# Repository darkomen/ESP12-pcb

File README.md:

# ESP12-pcb
Pcb for use an ESP12-e

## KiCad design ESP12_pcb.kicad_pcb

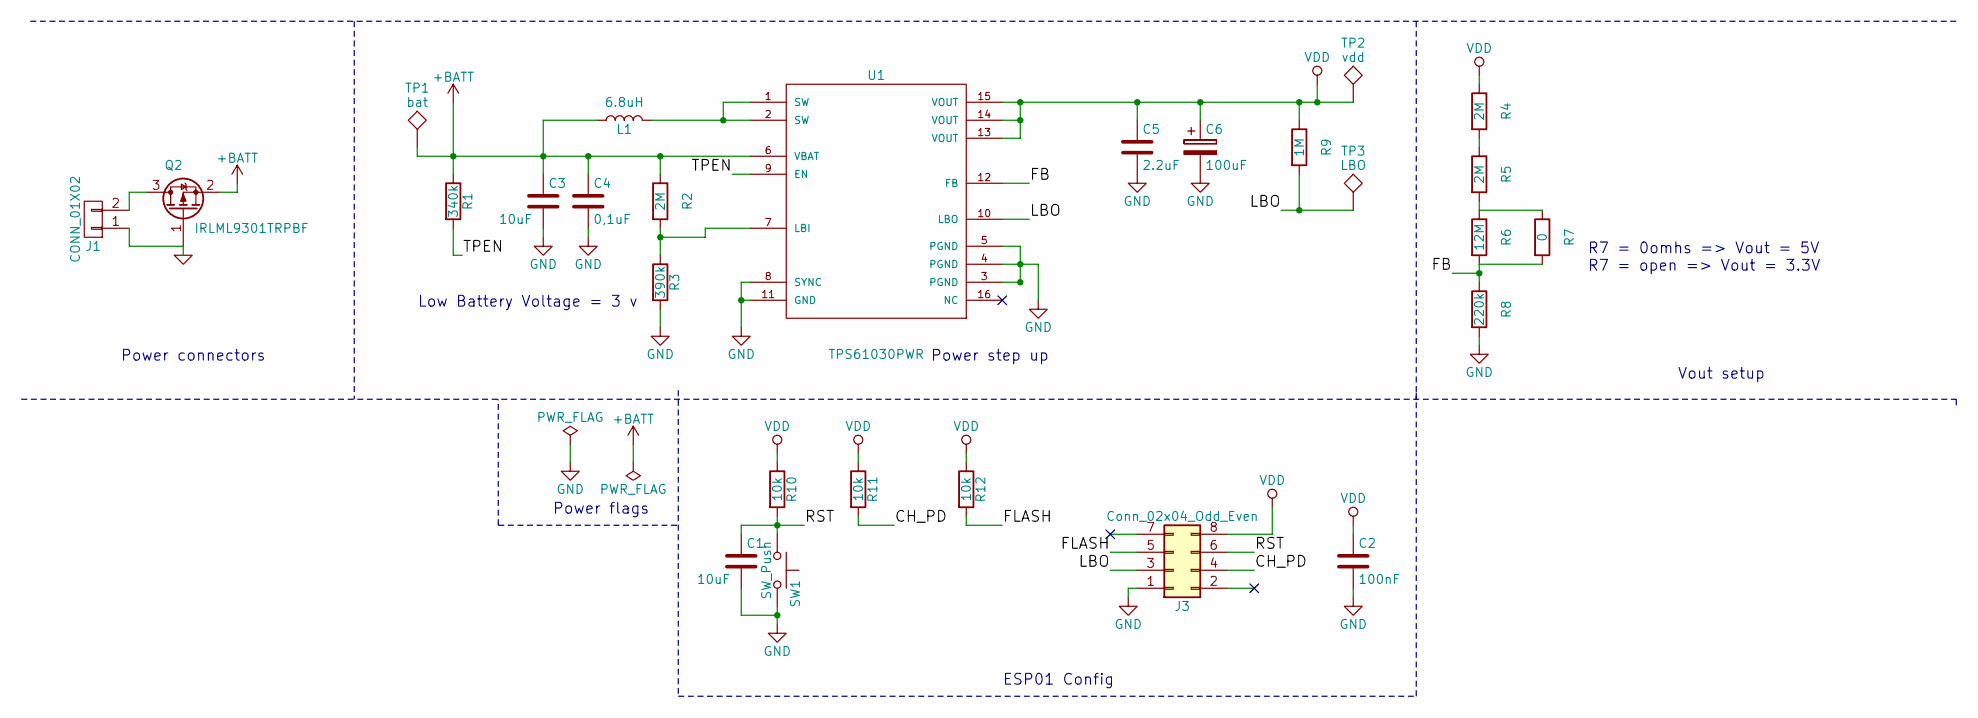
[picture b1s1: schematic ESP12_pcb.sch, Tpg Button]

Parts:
C1, C3: 10uF; C_0603_HandSoldering
C2: 100nF; C_0603_HandSoldering
C4: 0,1uF; C_0603_HandSoldering
C5: 2.2uF; C_0603_HandSoldering
C6: 100uF; smd_5_5.4
J1: CONN_01X02; Pin_Header_Straight_1x02_Pitch2.54mm
J3: Conn_02x04_Odd_Even; Pin_Header_Straight_2x04_Pitch2.54mm
L1: 6.8uH; smd_L_4532
Q2: IRLML9301TRPBF; SOT-23
R1: 340k; R_0603_HandSoldering
R2, R4, R5: 2M; R_0603_HandSoldering
R3: 390k; R_0603_HandSoldering
R6: 12M; R_0603_HandSoldering
R7: 0; R_0603_HandSoldering
R8: 220k; R_0603_HandSoldering
R9: 1M; R_0603_HandSoldering
R10, R11, R12: 10k; R_0603_HandSoldering
SW1: SW_Push; button_4pin
TP1: bat; Measurement_Point_Round-SMD-Pad_Small
TP2: vdd; Measurement_Point_Round-SMD-Pad_Small
TP3: LBO; Measurement_Point_Round-SMD-Pad_Small
U1: TPS61030PWR; R-PDSO-16

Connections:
+BATT: C3.1, C4.1, L1.1, Q2.2 (S), R1.1, R2.1, TP1.1, U1.6 (VBAT)
/CH_PD: J3.4, R11.2
/FB: R6.2, R7.2, R8.1, U1.12 (FB)
/FLASH: J3.5, R12.2
/LBO: J3.3, R9.2, TP3.1, U1.10 (LBO)
/RST: C1.1, J3.6, R10.2, SW1.1
/TPEN: R1.2, U1.9 (EN)
GND: C1.2, C2.2, C3.2, C4.2, C5.2, C6.2, J1.1, J3.1, Q2.1 (G), R3.2, R8.2, SW1.2, U1.3 (PGND), U1.4 (PGND), U1.5 (PGND), U1.8 (SYNC), U1.11 (GND)
unnamed: J1.2, Q2.3 (D)
unnamed: L1.2, U1.1 (SW), U1.2 (SW)
unnamed: R2.2, R3.1, U1.7 (LBI)
unnamed: R4.2, R5.1
unnamed: R5.2, R6.1, R7.1
VDD: C2.1, C5.1, C6.1, J3.8, R4.1, R9.1, R10.1, R11.1, R12.1, TP2.1, U1.13 (VOUT), U1.14 (VOUT), U1.15 (VOUT)

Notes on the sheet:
Low Battery Voltage = 3 v
Power connectors
Power step up
Power flags
R7 = 0omhs => Vout = 5V R7 = open => Vout = 3.3V
Vout setup
ESP01 Config

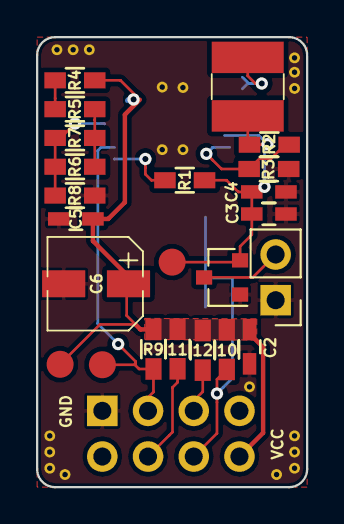
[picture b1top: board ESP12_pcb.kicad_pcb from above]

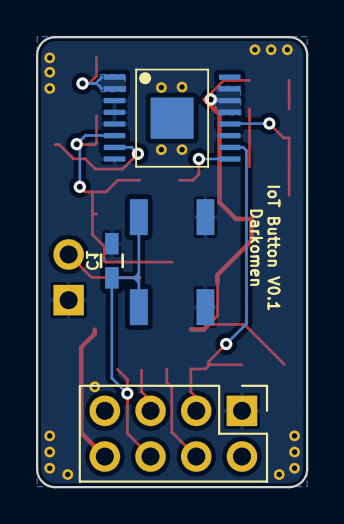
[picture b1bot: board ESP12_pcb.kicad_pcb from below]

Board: 2 copper layers, 15.0 x 25.0 mm, 27 parts (4 on the bottom side), 14 nets.

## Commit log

2017-08-17 Finished power components
2017-08-17 Gerber files has been generated
2017-08-18 Modified Top silk screen
2017-08-18 Gerber files updated
2017-08-21 Changed one connection for AP2112k
2017-08-21 BOM file generated
2017-10-11 Version V0.1 sended to fabrication
